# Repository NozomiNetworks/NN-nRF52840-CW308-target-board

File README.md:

# NN-nRF52840-CW308-target-board

An **open-source hardware design** for a [ChipWhisperer CW308 UFO](https://chipwhisperer.readthedocs.io/en/latest/Targets/CW308%20UFO.html) target board
featuring the [Nordic nRF52840](https://www.nordicsemi.com/Products/nRF52840), a modern ARM Cortex-M4 microcontroller with integrated BLE 5.4
connectivity commonly found in IoT and smart home devices. Designed for **hardware security research**, this board enables researchers and security
professionals to conduct side-channel analysis and fault-injection experiments on real-world IoT targets. The platform facilitates the study of
physical attack vectors against secure microcontrollers, supporting applications such as characterizing clock-glitch windows, analyzing power
consumption patterns, and validating the resilience of cryptographic implementations. Released under the open-source CERN-OHL-S v2 license, this
design empowers the security research community to reproduce, modify, and build upon cutting-edge defense mechanisms for embedded systems.

## Features

- Nordic **nRF52840** SoC (AQFN-73, 7 x 7 mm) — ARM Cortex-M4F @ 64 MHz, BLE 5.4 / 802.15.4 radio
- Standard **CW308 UFO 20-pin** interface (3 x 20-pin headers, J2/J3/J4)
- 32 MHz crystal with solder jumper (**JP1**) to AC-couple the CW308 **CLKIN** signal into the HF clock circuit — useful for clock-glitching experiments
- **CLKOUT** output (12 Ω series) so the target can clock the capture board
- 2.4 GHz radio: **U.FL** antenna connector (J1) with discrete pi-match (3.9 nH + 2 x 1 pF)
- NFC antenna connectors: 2-pin header (J5) and optional 5-pin, 0.5 mm-pitch **FPC** connector (J6)
- CW308 current-shunt sense lines (**SHUNTH**/SHUNTL) routed on-board (R1 = 12 Ω bridge, local decoupling)
- Powered from the CW308 3.3 V rail (VDD and VDDH tied to VCC)
- Standard CW308 form factor: 53.3 x 66.0 mm, 3 x M3 mounting holes

## Signal mapping

| UFO signal | nRF52840 pin | Notes |
|---|---|---|
| SCK | P0.26 | SPI |
| MISO | P0.04 | SPI |
| MOSI | P0.06 | SPI |
| GPIO1_TX | P1.13 | UART TX to CW308 |
| GPIO2_RX | P1.15 | UART RX from CW308 |
| GPIO3 | P0.02 | spare IO |
| GPIO4 | P0.29 | spare IO |
| LED1 | P0.24 | CW308 user LED |
| LED2 | P0.22 | CW308 user LED |
| LED3 | P0.20 | CW308 user LED |
| CLKIN | XC2 (via R2/C20 and JP1) | external clock injection |
| CLKOUT | P1.10 (via R3 = 12 Ω) | target clock to CW308 |
| HDR1 | P0.07 | spare IO |
| HDR2 | P1.09 | spare IO |
| HDR3 | P0.12 | spare IO |
| HDR4 | P0.13 | spare IO |
| HDR5 | P0.15 | spare IO |
| SWDIO | SWDIO | debug |
| SWDCLK | SWDCLK | debug |
| SWO | P1.00 | trace / debug |
| NRST | P0.18 | reset |
| NFC1 | P0.09 / NFC1 | NFC antenna |
| NFC2 | P0.10 / NFC2 | NFC antenna |

Programming and debugging are done through the CW308's onboard programmer (SWD), or by any external SWD adapter connected to the UFO.

## Repository layout

```
├── kicad_project/     KiCad schematic and PCB (nrf52840-ufo)
└── fabrication/       Gerbers, BOM and CPL ready for JLCPCB assembly
```

## Fabrication and assembly

- The files in `fabrication/` are prepared for **JLCPCB** assembly; the BOM includes the corresponding LCSC part numbers (e.g. `C190794` for the nRF52840-QIAA-R).
- The U.FL connector, the 20-pin UFO headers and the NFC pin header are **excluded from assembly** and must be sourced and soldered separately if needed.
- `C13`, `C16` and `C4` are DNP (no-connect placeholders kept for matching/tuning options).

## License

Hardware released under the **CERN Open Hardware Licence Version 2 - Strongly Reciprocal** (CERN-OHL-S-2.0). See [LICENSE](LICENSE).

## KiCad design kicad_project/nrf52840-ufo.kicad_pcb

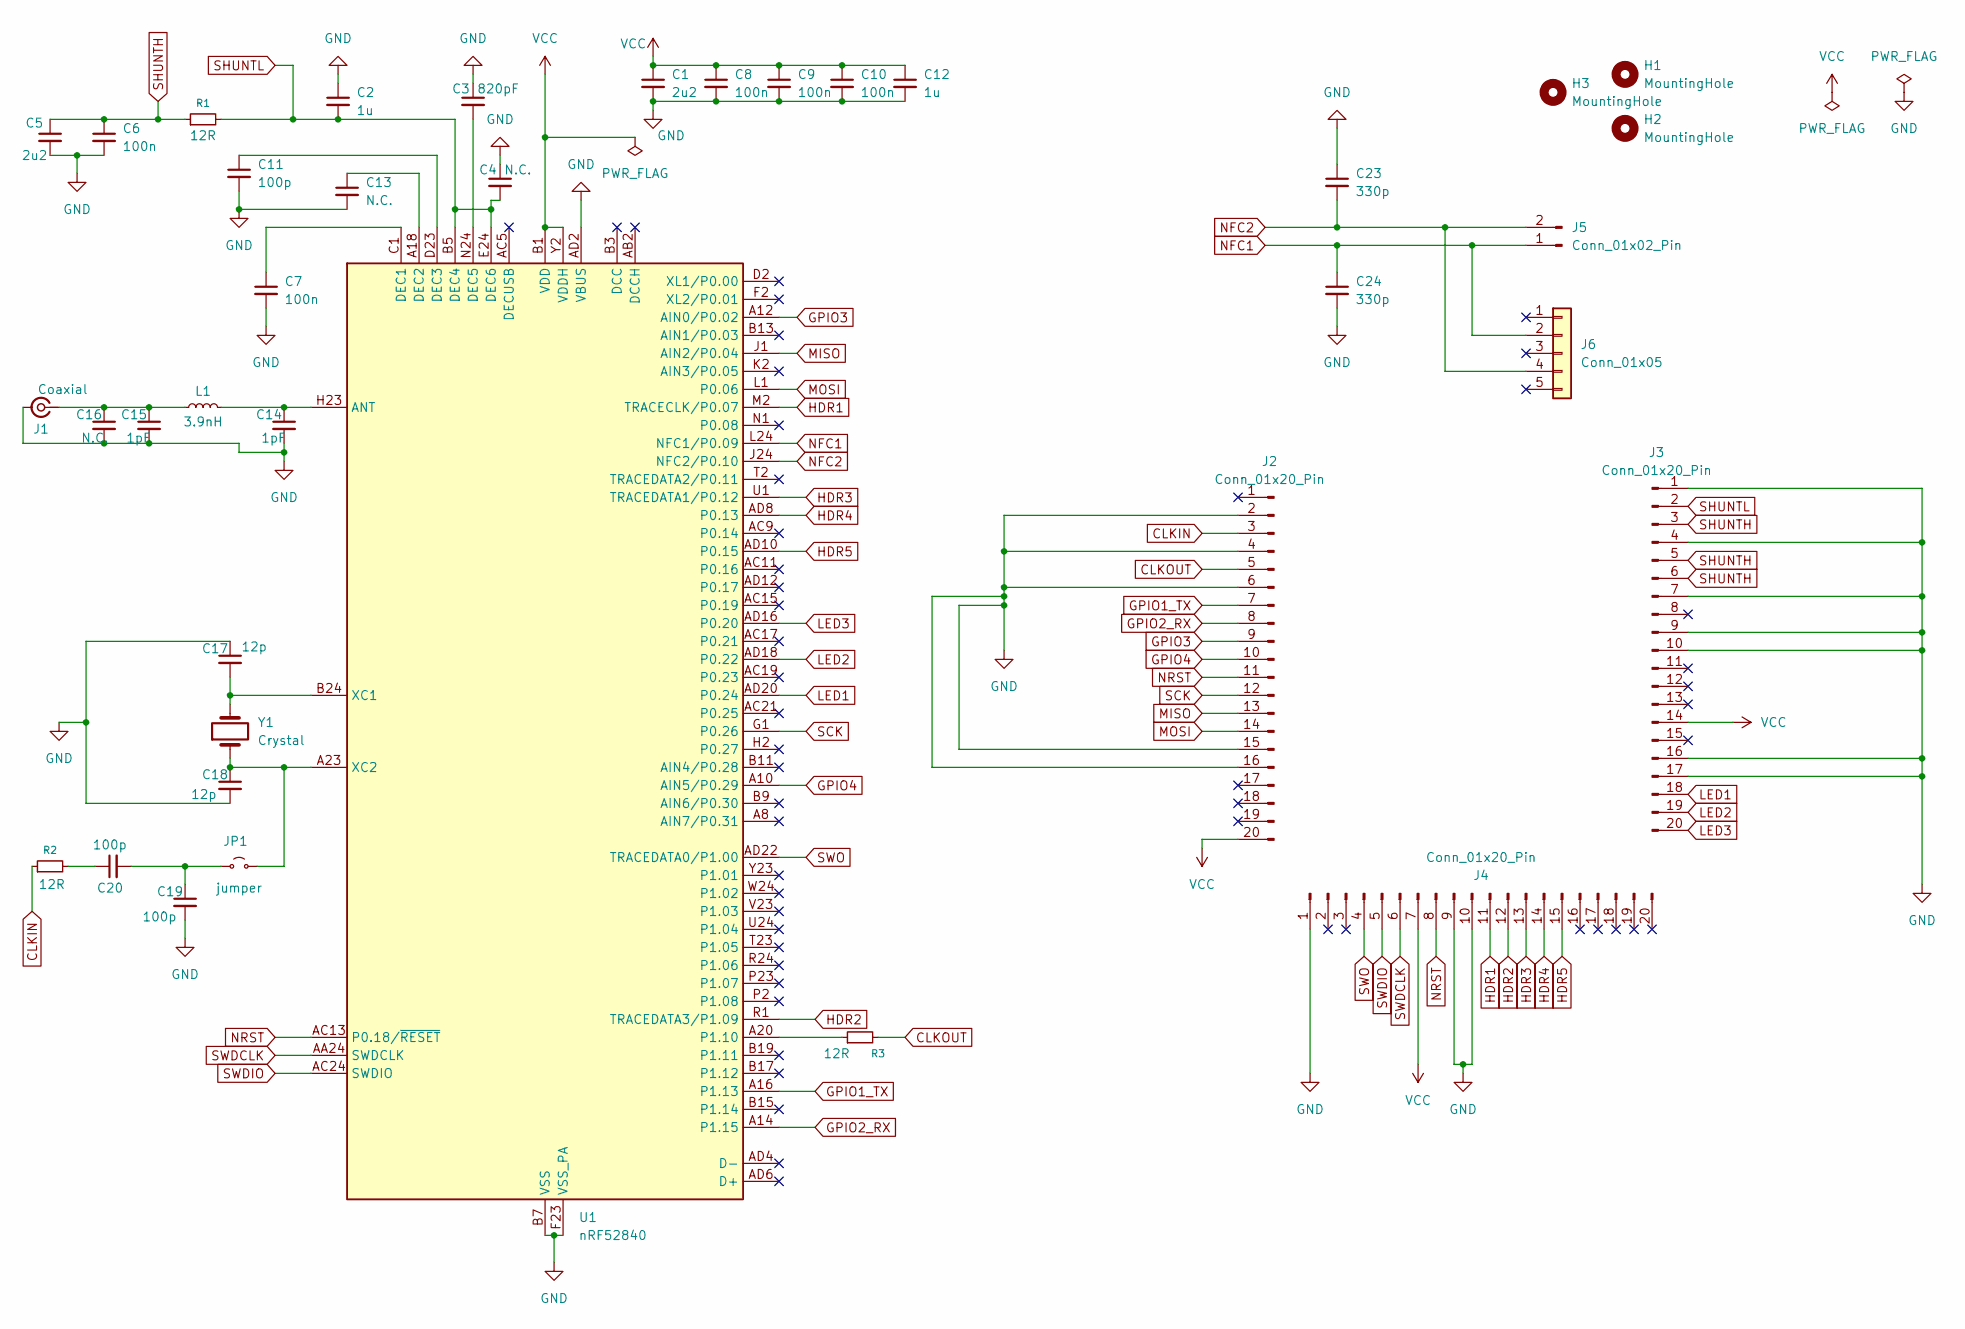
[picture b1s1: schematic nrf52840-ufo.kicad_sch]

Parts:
C1, C5: 2u2; C_0603_1608Metric_Pad1.08x0.95mm_HandSolder
C2, C12: 1u; C_0603_1608Metric_Pad1.08x0.95mm_HandSolder
C3: 820pF; C_0402_1005Metric_Pad0.74x0.62mm_HandSolder
C4, C13, C16: N.C.; C_0402_1005Metric_Pad0.74x0.62mm_HandSolder
C6, C7, C8, C9, C10: 100n; C_0603_1608Metric_Pad1.08x0.95mm_HandSolder
C11: 100p; C_0402_1005Metric_Pad0.74x0.62mm_HandSolder
C14, C15: 1pF; C_0402_1005Metric_Pad0.74x0.62mm_HandSolder
C17, C18: 12p; C_0402_1005Metric_Pad0.74x0.62mm_HandSolder
C19, C20: 100p; C_0603_1608Metric_Pad1.08x0.95mm_HandSolder
C23, C24: 330p; C_0603_1608Metric_Pad1.08x0.95mm_HandSolder
H1, H2, H3: MountingHole; MountingHole_3.2mm_M3_DIN965_Pad
J1: Coaxial; U.FL_Molex_MCRF_73412-0110_Vertical
J2, J3, J4: Conn_01x20_Pin; PinHeader_1x20_P2.54mm_Vertical
J5: Conn_01x02_Pin; PinHeader_1x02_P2.54mm_Vertical
J6: Conn_01x05; TE_0-1734839-5_1x05-1MP_P0.5mm_Horizontal
JP1: jumper; SolderJumper-2_P1.3mm_Open_RoundedPad1.0x1.5mm
L1: 3.9nH; L_0402_1005Metric_Pad0.77x0.64mm_HandSolder
R1, R2, R3: 12R; R_0603_1608Metric_Pad0.98x0.95mm_HandSolder
U1: nRF52840; Nordic_AQFN-73-1EP_7x7mm_P0.5mm
Y1: Crystal; Crystal_SMD_3215-2Pin_3.2x1.5mm

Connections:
CLKIN: J2.3, R2.1
CLKOUT: J2.5, R3.2
GND: C1.2, C2.1, C3.1, C4.1, C5.2, C6.2, C7.2, C8.2, C9.2, C10.2, C11.2, C12.2, C13.2, C14.2, C15.2, C16.2, C17.1, C18.2, C19.2, C23.1, C24.2, J1.2 (Ext), J2.2, J2.4, J2.6, J2.15, J2.16, J3.1, J3.4, J3.7, J3.9, J3.10, J3.16, J3.17, J4.1, J4.9, J4.10, U1.AD2 (VBUS), U1.B7 (VSS), U1.EP (VSS), U1.F23 (VSS_PA)
GPIO1_TX: J2.7, U1.A16 (P1.13)
GPIO2_RX: J2.8, U1.A14 (P1.15)
GPIO3: J2.9, U1.A12 (AIN0/P0.02)
GPIO4: J2.10, U1.A10 (AIN5/P0.29)
HDR1: J4.11, U1.M2 (TRACECLK/P0.07)
HDR2: J4.12, U1.R1 (TRACEDATA3/P1.09)
HDR3: J4.13, U1.U1 (TRACEDATA1/P0.12)
HDR4: J4.14, U1.AD8 (P0.13)
HDR5: J4.15, U1.AD10 (P0.15)
LED1: J3.18, U1.AD20 (P0.24)
LED2: J3.19, U1.AD18 (P0.22)
LED3: J3.20, U1.AD16 (P0.20)
MISO: J2.13, U1.J1 (AIN2/P0.04)
MOSI: J2.14, U1.L1 (P0.06)
NFC1: C24.1, J5.1, J6.2, U1.L24 (NFC1/P0.09)
NFC2: C23.2, J5.2, J6.4, U1.J24 (NFC2/P0.10)
NRST: J2.11, J4.8, U1.AC13 (P0.18/~RESET)
unnamed: C20.1, R2.2
unnamed: C15.1, C16.1, J1.1 (In), L1.1
unnamed: C19.1, C20.2, JP1.1 (A)
unnamed: C18.1, JP1.2 (B), U1.A23 (XC2), Y1.1
unnamed: C14.1, L1.2, U1.H23 (ANT)
unnamed: C7.1, U1.C1 (DEC1)
unnamed: C13.1, U1.A18 (DEC2)
unnamed: C11.1, U1.D23 (DEC3)
unnamed: C3.2, U1.N24 (DEC5)
unnamed: R3.1, U1.A20 (P1.10)
unnamed: C17.2, U1.B24 (XC1), Y1.2
SCK: J2.12, U1.G1 (P0.26)
SHUNTH: C5.1, C6.1, J3.3, J3.5, J3.6, R1.1
SHUNTL: C2.2, C4.2, J3.2, R1.2, U1.B5 (DEC4), U1.E24 (DEC6)
SWDCLK: J4.6, U1.AA24 (SWDCLK)
SWDIO: J4.5, U1.AC24 (SWDIO)
SWO: J4.4, U1.AD22 (TRACEDATA0/P1.00)
VCC: C1.1, C8.1, C9.1, C10.1, C12.1, J2.20, J3.14, J4.7, U1.A22 (VDD), U1.AD14 (VDD), U1.AD23 (VDD), U1.B1 (VDD), U1.W1 (VDD), U1.Y2 (VDDH)

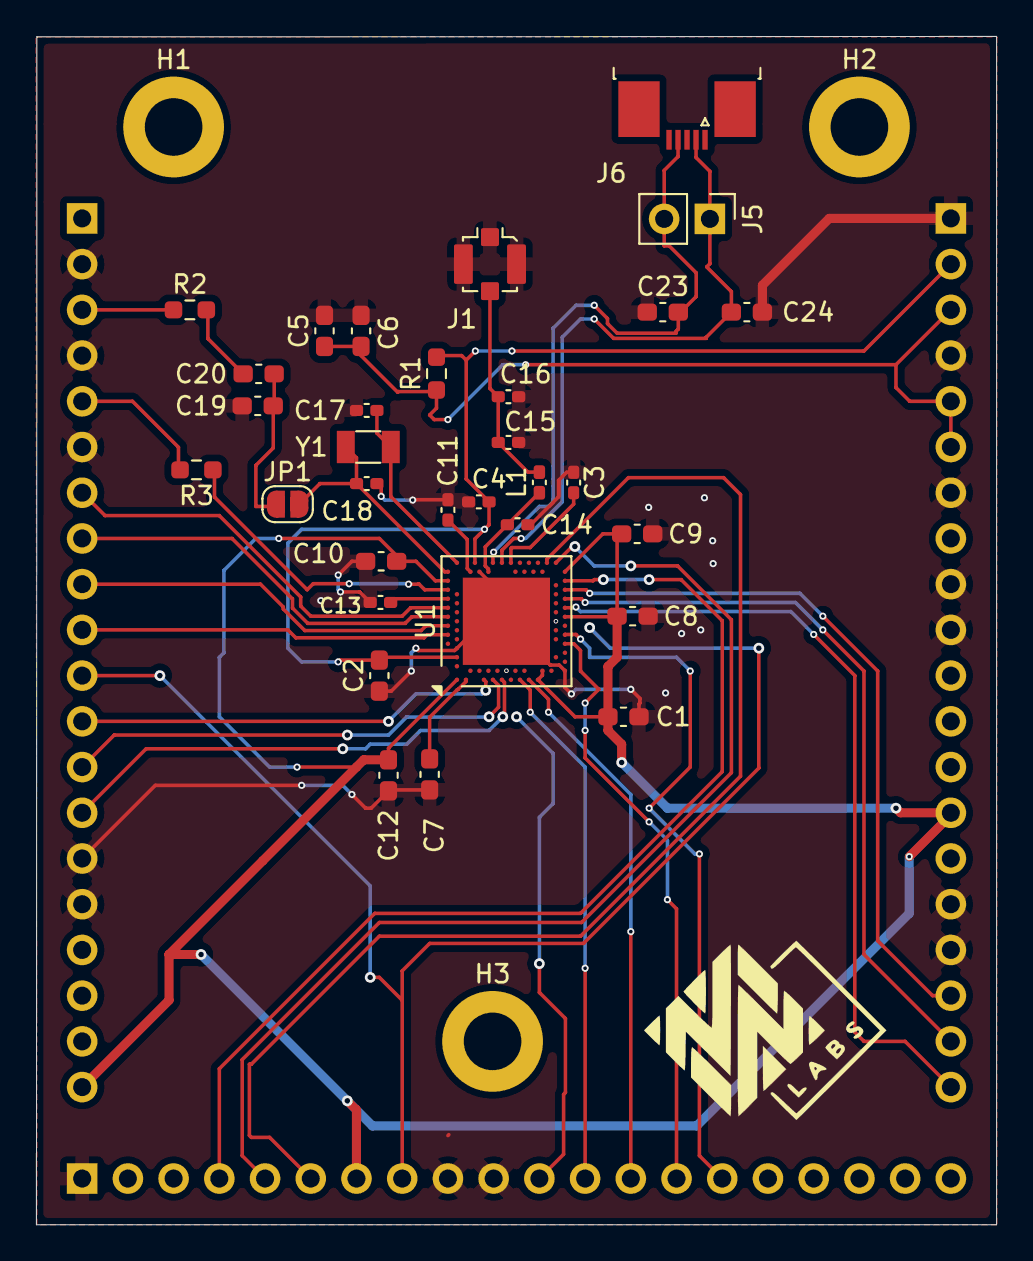
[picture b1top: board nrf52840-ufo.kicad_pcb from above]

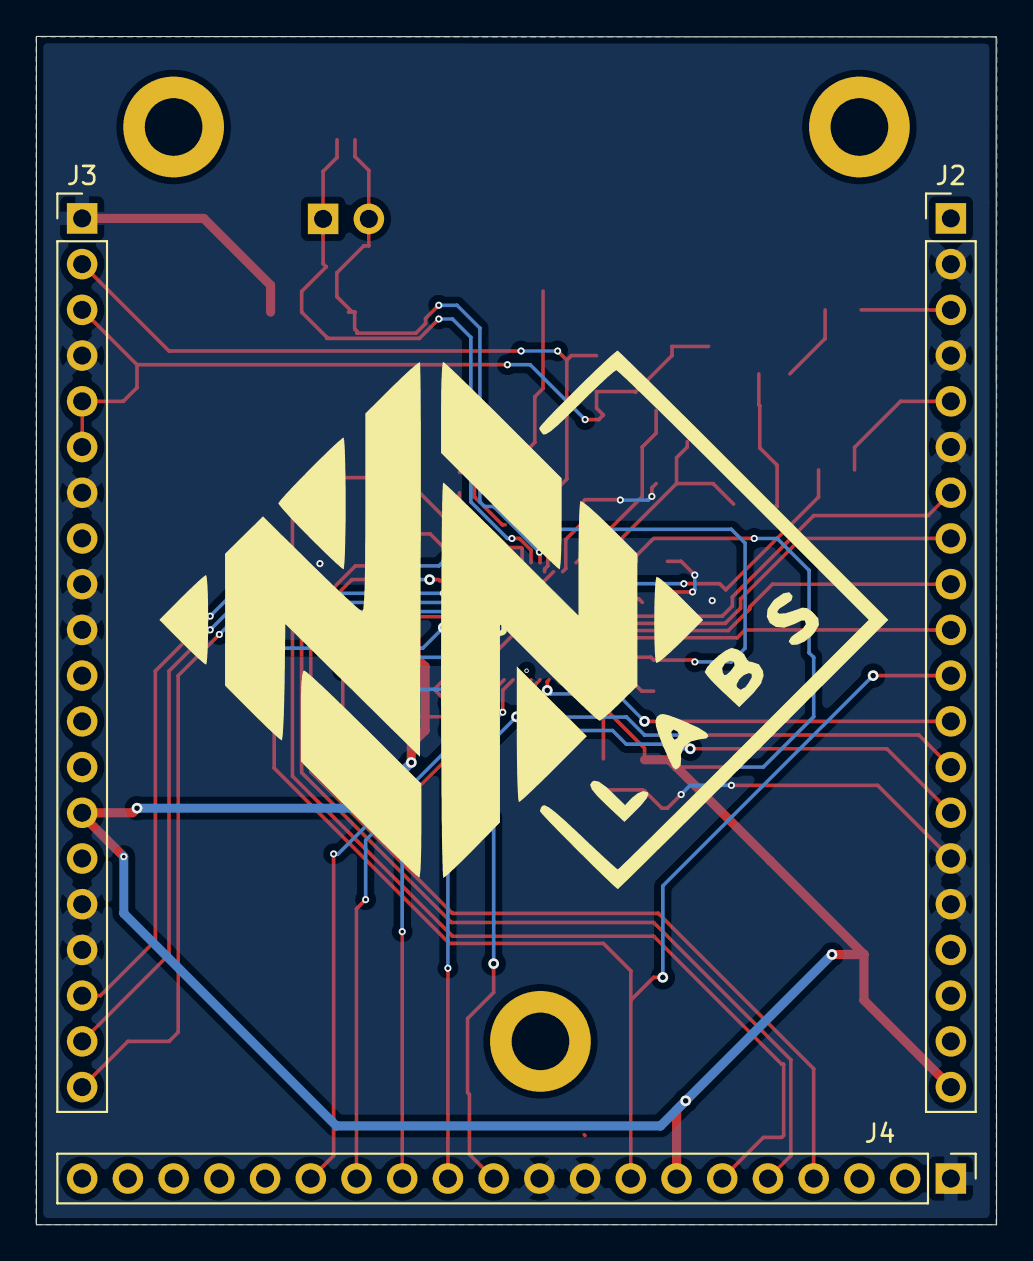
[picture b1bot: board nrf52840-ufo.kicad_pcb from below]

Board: 4 copper layers, 53.3 x 66.0 mm, 38 parts (3 on the bottom side), 38 nets.

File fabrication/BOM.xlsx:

Comment | Designator | Footprint | JLCPCB Part #（optional）
2u2 | C1,C5 | Capacitor_SMD:C_0603_1608Metric_Pad1.08x0.95mm_HandSolder | C23630
1u | C2,C12 | Capacitor_SMD:C_0603_1608Metric_Pad1.08x0.95mm_HandSolder | C1592
820pF | C3 | Capacitor_SMD:C_0402_1005Metric_Pad0.74x0.62mm_HandSolder | C107031
100n | C6,C7,C8,C9,C10 | Capacitor_SMD:C_0603_1608Metric_Pad1.08x0.95mm_HandSolder | C14663
100p | C11 | Capacitor_SMD:C_0402_1005Metric_Pad0.74x0.62mm_HandSolder | C1546
1pF | C14,C15 | Capacitor_SMD:C_0402_1005Metric_Pad0.74x0.62mm_HandSolder | C1550
12p | C17,C18 | Capacitor_SMD:C_0402_1005Metric_Pad0.74x0.62mm_HandSolder | C1547
100p | C19,C20 | Capacitor_SMD:C_0603_1608Metric_Pad1.08x0.95mm_HandSolder | C14858
330p | C23,C24 | Capacitor_SMD:C_0603_1608Metric_Pad1.08x0.95mm_HandSolder | C1664
Conn_01x05 | J6 | Connector_FFC-FPC:TE_0-1734839-5_1x05-1MP_P0.5mm_Horizontal | C5162928
3.9nH | L1 | Inductor_SMD:L_0402_1005Metric_Pad0.77x0.64mm_HandSolder | C186836
12R | R1,R2,R3 | Resistor_SMD:R_0603_1608Metric_Pad0.98x0.95mm_HandSolder | C2906990
nRF52840 | U1 | Package_DFN_QFN:Nordic_AQFN-73-1EP_7x7mm_P0.5mm | C190794
Crystal | Y1 | Crystal:Crystal_SMD_3215-2Pin_3.2x1.5mm | C284175
